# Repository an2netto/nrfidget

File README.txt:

A POV fidget spinner based on nRF52832

pcb - KiCAD design
sim - a simulator with 74HC595 shift register, SS413A Hall sensor and Nokia 5110 LCD

still in progress

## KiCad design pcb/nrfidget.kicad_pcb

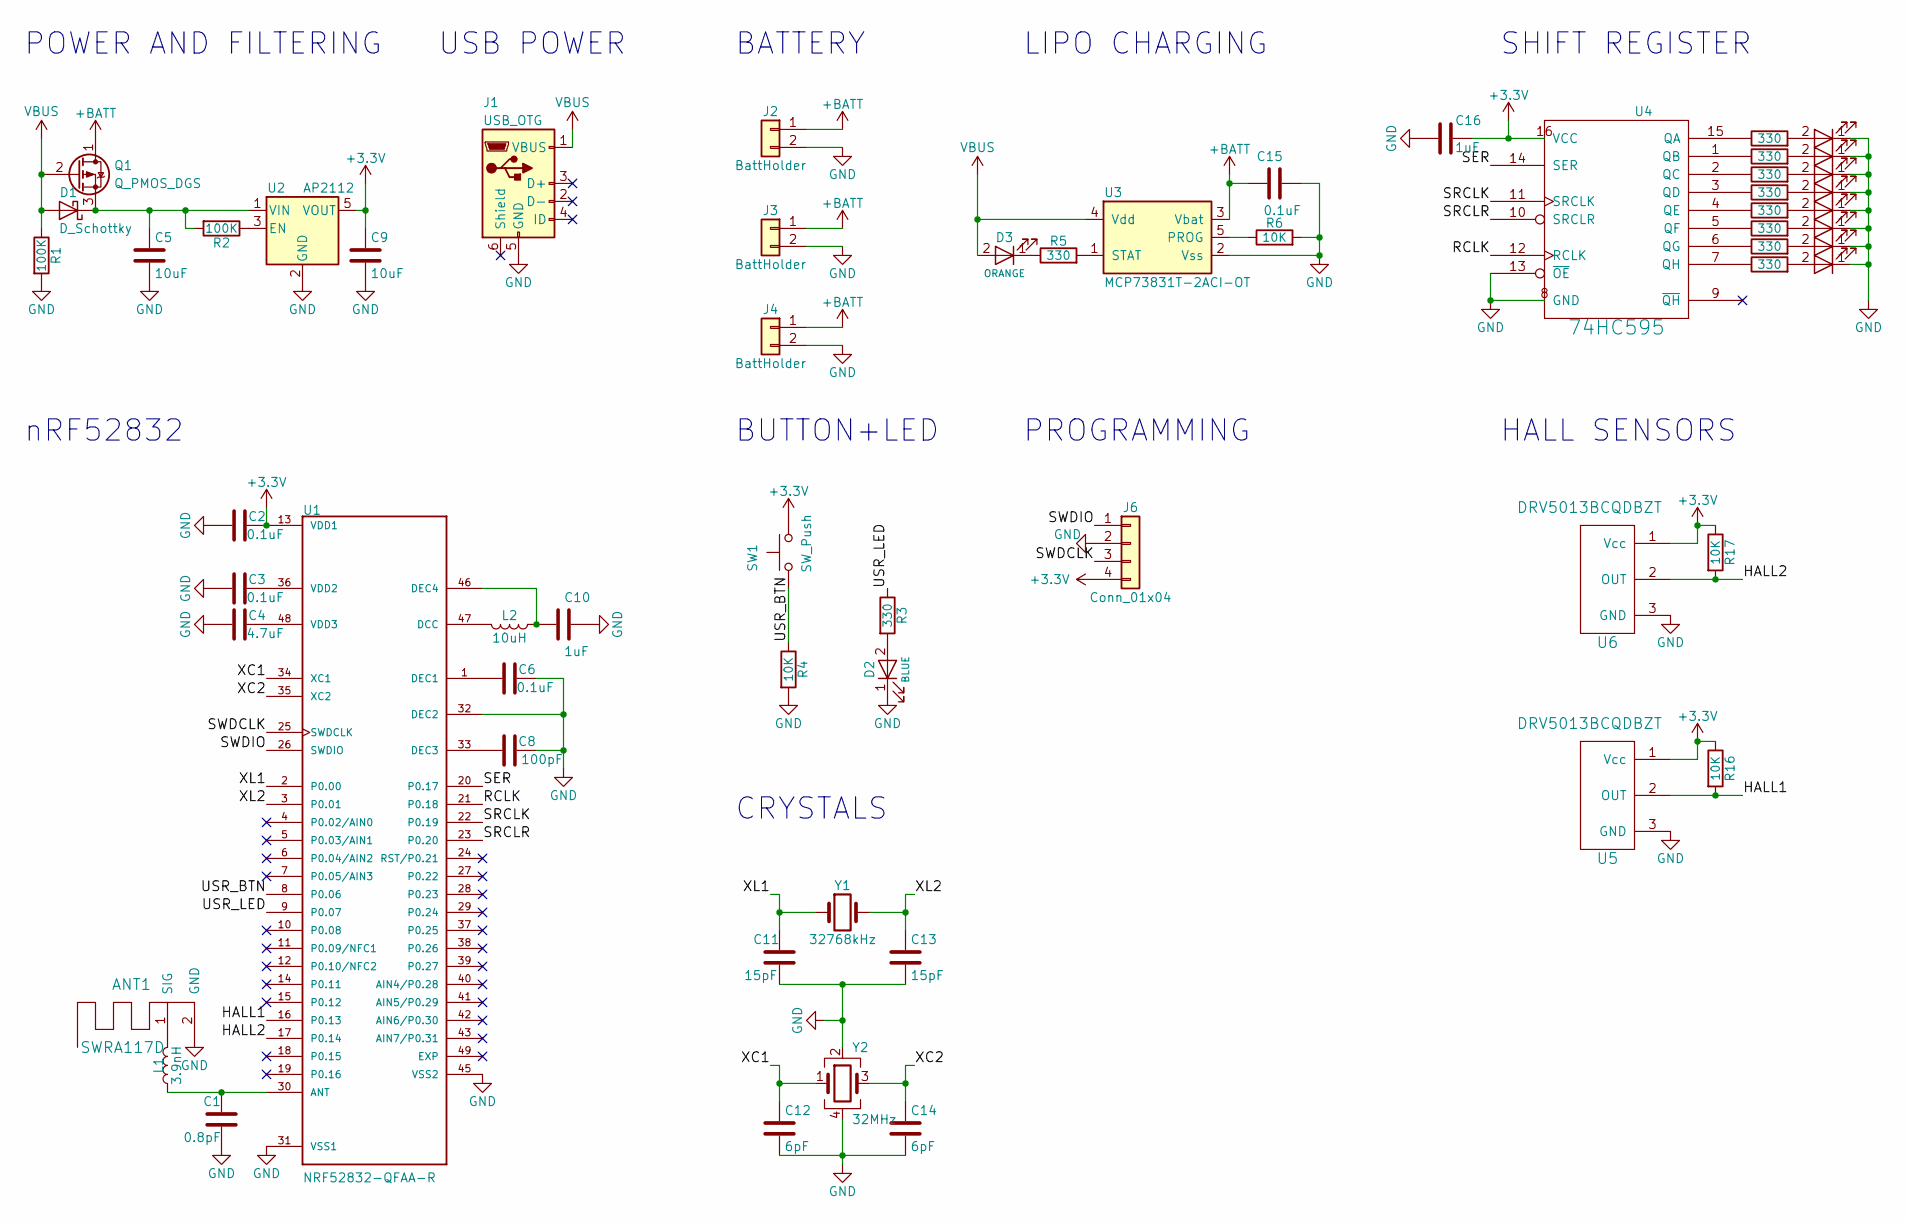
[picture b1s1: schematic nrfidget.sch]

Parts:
ANT1: SWRA117D; Texas_SWRA117D_2.4GHz_Left
C1: 0.8pF; C_0402
C2, C3, C6, C15: 0.1uF; C_0402
C4: 4.7uF; C_0603_HandSoldering
C5, C9: 10uF; C_0603_HandSoldering
C8: 100pF; C_0402
C10: 1uF; C_0603_HandSoldering
C11, C13: 15pF; C_0402
C12, C14: 6pF; C_0402
C16: 1uF; C_0402
D1: D_Schottky; D_SOD-123
D2: BLUE; LED_0603_HandSoldering
D3: ORANGE; LED_0603_HandSoldering
D4, D5, D6, D7, D8, D9, D10, D11: LED; LED_0603_HandSoldering
J1: USB_OTG; USB_Micro-B_Molex-105017-0001
J2, J3, J4: BattHolder; 3003
J6: Conn_01x04; Pin_Header_Straight_1x04_Pitch1.27mm
L1: 3.9nH; L_0402
L2: 10uH; L_0603_HandSoldering
Q1: Q_PMOS_DGS; SOT-23_Handsoldering
R1, R2: 100K; R_0402
R3, R5, R7, R8, R9, R10, R11, R12, R13, R14: 330; R_0402
R4, R6, R16, R17: 10K; R_0402
SW1: SW_Push; SW_SPST_PTS645
U1: NRF52832-QFAA-R; QFN-48-1EP_6x6mm_P0.4mm_EP4.66x4.66mm
U2: AP2112; SOT-23-5
U3: MCP73831T-2ACI-OT; SOT-23-5
U4: 74HC595; TSSOP-16_4.4x5mm_P0.65mm
U5, U6: DRV5013BCQDBZT; SOT-23
Y1: 32768kHz; Crystal_SMD_3215-2pin_3.2x1.5mm
Y2: 32MHz; Crystal_SMD_2016-4pin_2.0x1.6mm

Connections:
+3V3: C2.2, C9.1, C16.1, J6.4, R16.1, R17.1, SW1.1, U1.13 (VDD1), U2.5 (VOUT), U4.16 (VCC), U5.1 (Vcc), U6.1 (Vcc)
+BATT: C15.1, J2.1, J3.1, J4.1, Q1.1 (D), U3.3 (Vbat)
/HALL1: R16.2, U1.16 (P0.13), U5.2 (OUT)
/HALL2: R17.2, U1.17 (P0.14), U6.2 (OUT)
/RCLK: U1.21 (P0.18), U4.12 (RCLK)
/SER: U1.20 (P0.17), U4.14 (SER)
/SRCLK: U1.22 (P0.19), U4.11 (SRCLK)
/SRCLR: U1.23 (P0.20), U4.10 (SRCLR)
/SWDCLK: J6.3, U1.25 (SWDCLK)
/SWDIO: J6.1, U1.26 (SWDIO)
/USR_BTN: R4.1, SW1.2, U1.8 (P0.06)
/USR_LED: R3.1, U1.9 (P0.07)
/XC1: C12.1, U1.34 (XC1), Y2.1
/XC2: C14.1, U1.35 (XC2), Y2.3
/XL1: C11.1, U1.2 (P0.00), Y1.1
/XL2: C13.1, U1.3 (P0.01), Y1.2
GND: ANT1.2 (GND), C1.2, C2.1, C3.1, C4.1, C5.2, C6.2, C8.2, C9.2, C10.1, C11.2, C12.2, C13.2, C14.2, C15.2, C16.2, D2.1 (K), D4.1 (K), D5.1 (K), D6.1 (K), D7.1 (K), D8.1 (K), D9.1 (K), D10.1 (K), D11.1 (K), J1.5 (GND), J2.2, J3.2, J4.2, J6.2, R1.2, R4.2, R6.2, U1.31 (VSS1), U1.32 (DEC2), U1.45 (VSS2), U1.49 (EXP), U2.2 (GND), U3.2 (Vss), U4.8 (GND), U4.13 (~OE), U5.3 (GND), U6.3 (GND), Y2.2, Y2.4
unnamed: ANT1.1 (SIG), L1.1
unnamed: C1.1, L1.2, U1.30 (ANT)
unnamed: C3.2, U1.36 (VDD2)
unnamed: C4.2, U1.48 (VDD3)
unnamed: C5.1, D1.1 (K), Q1.3 (S), R2.2, U2.1 (VIN)
unnamed: C6.1, U1.1 (DEC1)
unnamed: C8.1, U1.33 (DEC3)
unnamed: C10.2, L2.1, U1.46 (DEC4)
unnamed: D2.2 (A), R3.2
unnamed: D3.1 (K), R5.1
unnamed: D4.2 (A), R7.2
unnamed: D5.2 (A), R8.2
unnamed: D6.2 (A), R9.2
unnamed: D7.2 (A), R10.2
unnamed: D8.2 (A), R11.2
unnamed: D9.2 (A), R12.2
unnamed: D10.2 (A), R13.2
unnamed: D11.2 (A), R14.2
unnamed: L2.2, U1.47 (DCC)
unnamed: R2.1, U2.3 (EN)
unnamed: R5.2, U3.1 (STAT)
unnamed: R6.1, U3.5 (PROG)
unnamed: R7.1, U4.15 (QA)
unnamed: R8.1, U4.1 (QB)
unnamed: R9.1, U4.2 (QC)
unnamed: R10.1, U4.3 (QD)
unnamed: R11.1, U4.4 (QE)
unnamed: R12.1, U4.5 (QF)
unnamed: R13.1, U4.6 (QG)
unnamed: R14.1, U4.7 (QH)
VBUS: D1.2 (A), D3.2 (A), J1.1 (VBUS), Q1.2 (G), R1.1, U3.4 (Vdd)

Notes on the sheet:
SHIFT REGISTER
BUTTON+LED
BATTERY
USB POWER
POWER AND FILTERING
nRF52832
CRYSTALS
LIPO CHARGING
PROGRAMMING
HALL SENSORS

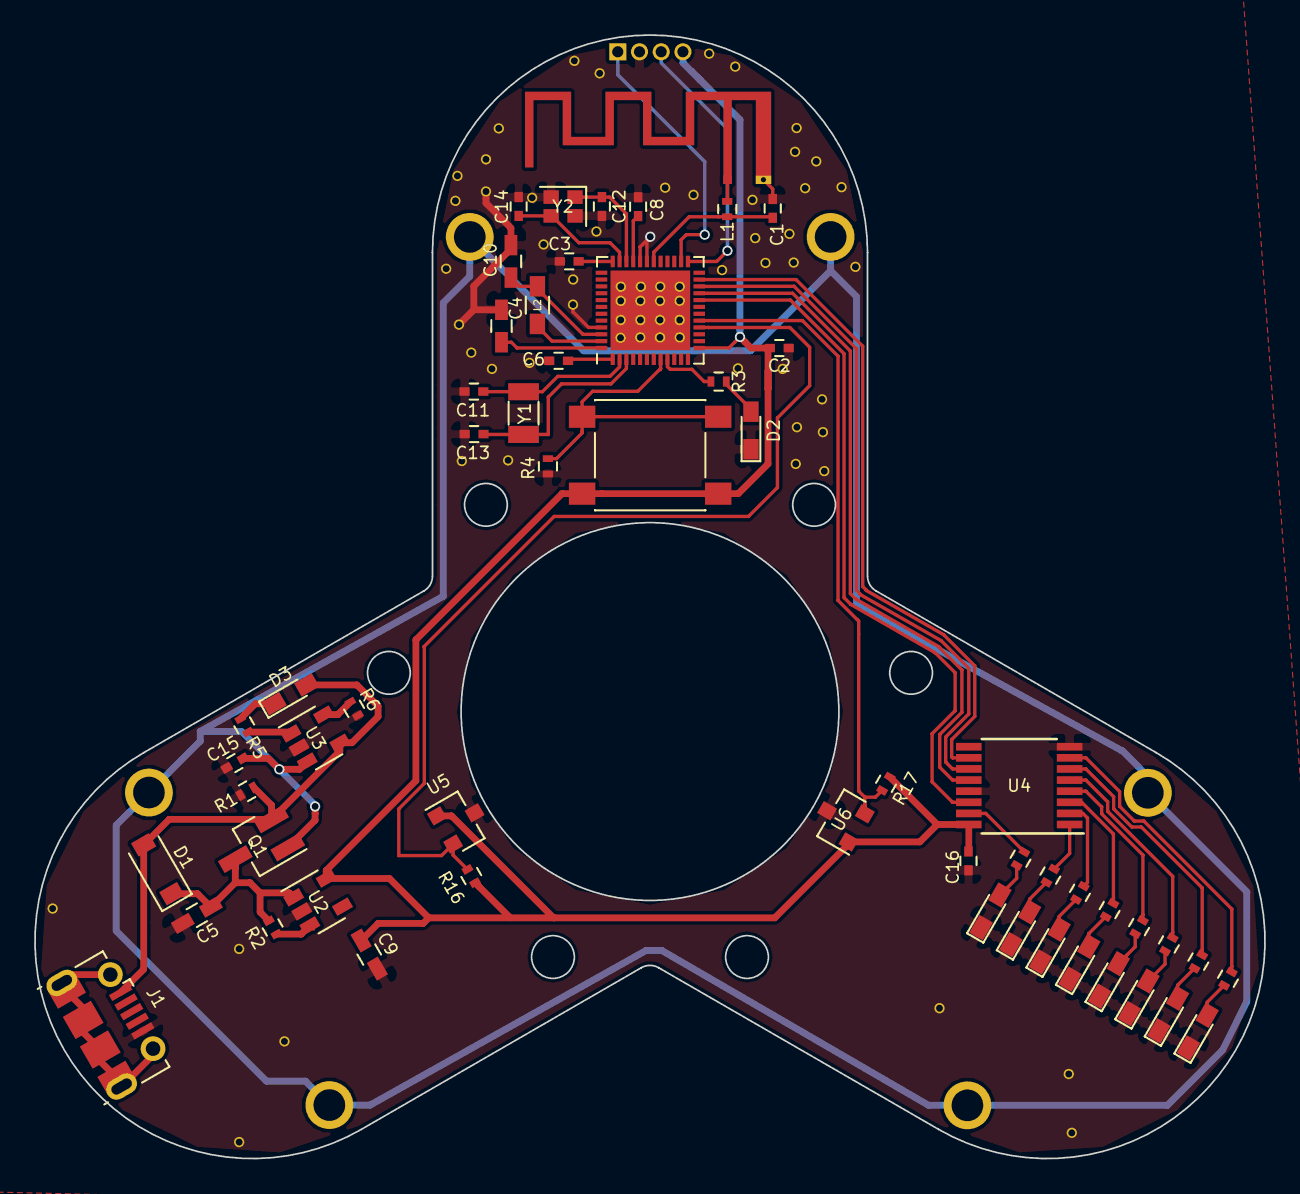
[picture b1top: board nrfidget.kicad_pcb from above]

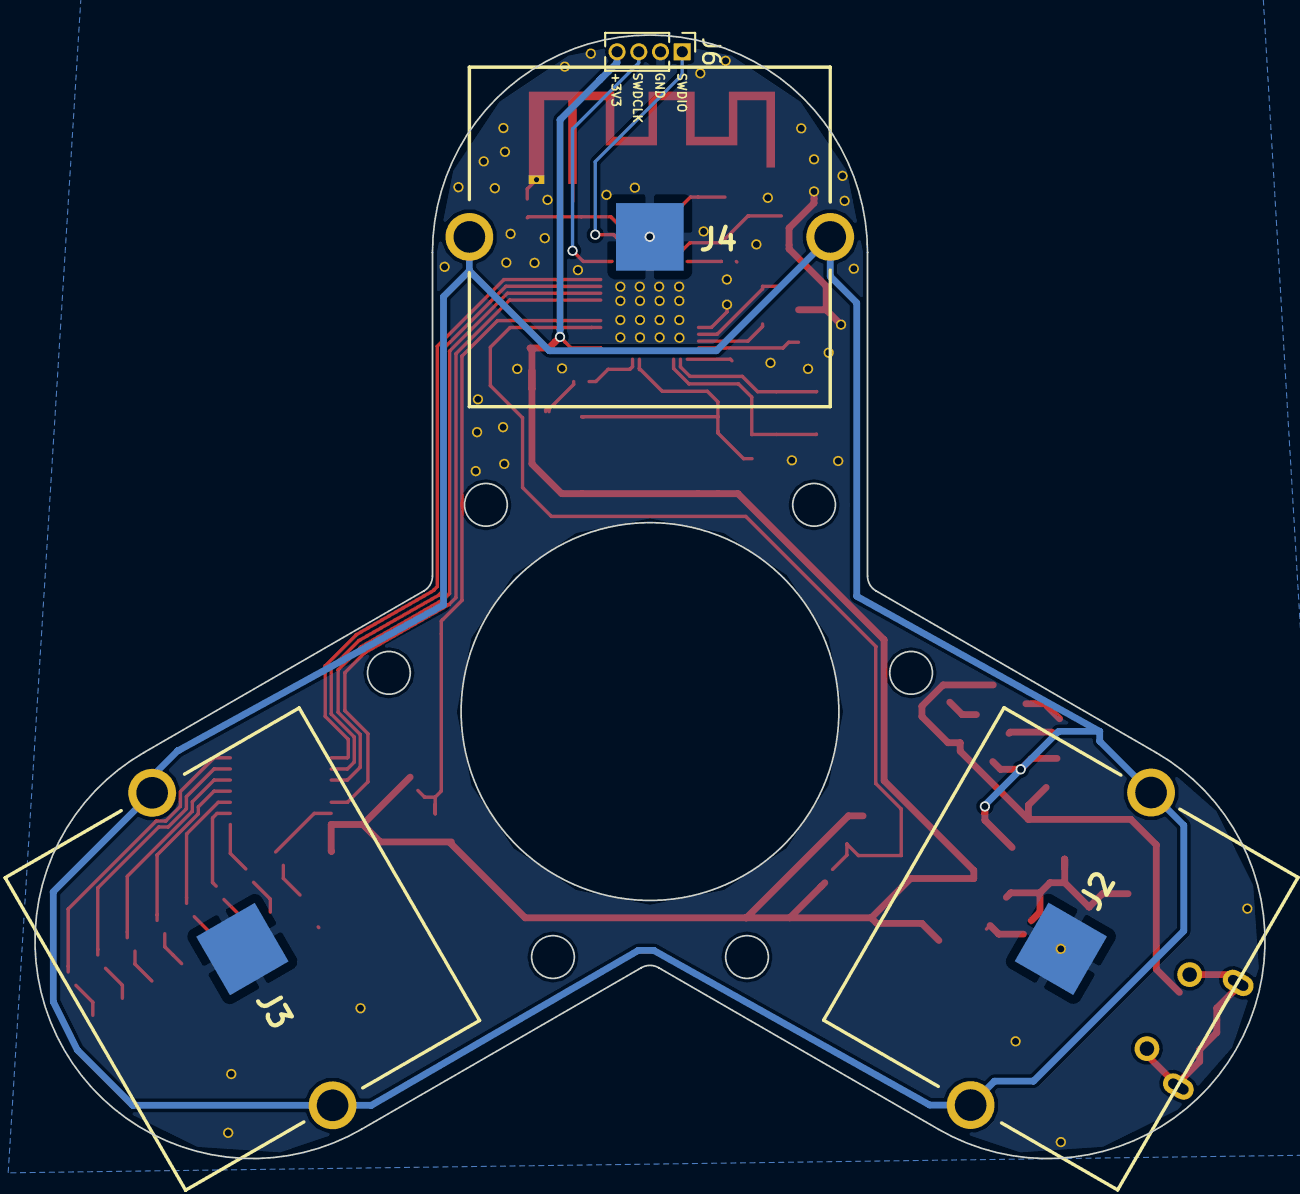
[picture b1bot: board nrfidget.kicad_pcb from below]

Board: 2 copper layers, 71.9 x 65.7 mm, 60 parts (4 on the bottom side), 48 nets.

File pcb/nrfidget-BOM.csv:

Refs,value,manpt#,shop,datasheet,footprint,
ANT1,SWRA117D,,,,RF_Antenna:Texas_SWRA117D_2.4GHz_Left,
C1,0.8pF,GJM1555C1HR80WB01D,,,Capacitors_SMD:C_0402,
C10,1uF,GCM188R71C105KA64D,https://www.rcscomponents.kiev.ua/product/1uf-16v-x7r-10-060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,,Capacitors_SMD:C_0603_HandSoldering,
C11,12pF,C0402N120J500NU-Hitano,https://www.rcscomponents.kiev.ua/product/12pf-50v-5-np0-040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,,Capacitors_SMD:C_0402,
C12,12pF,C0402N120J500NU-Hitano,https://www.rcscomponents.kiev.ua/product/12pf-50v-5-np0-040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,,Capacitors_SMD:C_0402,
C13,12pF,C0402N120J500NU-Hitano,https://www.rcscomponents.kiev.ua/product/12pf-50v-5-np0-040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,,Capacitors_SMD:C_0402,
C14,12pF,C0402N120J500NU-Hitano,https://www.rcscomponents.kiev.ua/product/12pf-50v-5-np0-040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,,Capacitors_SMD:C_0402,
C15,0.1uF,100nF 50V 10% X7R,https://www.rcscomponents.kiev.ua/product/100nf-50v-10-x7r-0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 ,,Capacitors_SMD:C_0402,
C16,1uF,"1uF 6,3V 10% X5R",https://www.rcscomponents.kiev.ua/product/1uf-6-3v-10-x5r-04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,,Capacitors_SMD:C_0402,
C2,0.1uF,100nF 50V 10% X7R,https://www.rcscomponents.kiev.ua/product/100nf-50v-10-x7r-0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 ,,Capacitors_SMD:C_0402,
C3,0.1uF,100nF 50V 10% X7R,https://www.rcscomponents.kiev.ua/product/100nf-50v-10-x7r-0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 ,,Capacitors_SMD:C_0402,
C4,4.7uF,"4,7uF 6,3V X5R 10%",https://www.rcscomponents.kiev.ua/product/4-7uf-6-3v-x5r-10-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,,Capacitors_SMD:C_0603_HandSoldering,
C5,10uF,"10uF 6,3V X5R 10%",https://www.rcscomponents.kiev.ua/product/10uf-6-3v-x5r-10-0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,,Capacitors_SMD:C_0603_HandSoldering,
C6,0.1uF,100nF 50V 10% X7R,https://www.rcscomponents.kiev.ua/product/100nf-50v-10-x7r-0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 ,,Capacitors_SMD:C_0402,
C8,100pF,100pF 50V 5% NP0,https://www.rcscomponents.kiev.ua/product/100pf-50v-5-np0-04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,,Capacitors_SMD:C_0402,
C9,10uF,"10uF 6,3V X5R 10%",https://www.rcscomponents.kiev.ua/product/10uf-6-3v-x5r-10-0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,,Capacitors_SMD:C_0603_HandSoldering,
D1,D_Schottky,MBR120LSFT1G,https://imrad.com.ua/ru/mbr120lsft1g,,Diodes_SMD:D_SOD-123,
D10,LED,LTST-C190TBKT,https://www.rcscomponents.kiev.ua/product/ltst-c190tbkt_121694.html,,LEDs:LED_0603_HandSoldering,
D11,LED,LTST-C190TBKT,https://www.rcscomponents.kiev.ua/product/ltst-c190tbkt_121694.html,,LEDs:LED_0603_HandSoldering,
D2,BLUE,LTST-C190TBKT,https://www.rcscomponents.kiev.ua/product/ltst-c190tbkt_121694.html,,LEDs:LED_0603_HandSoldering,
D3,ORANGE,KPT-1608SEW-E-Kingbright,https://www.rcscomponents.kiev.ua/product/svetodiod-0603-ora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,,LEDs:LED_0603_HandSoldering,
D4,LED,LTST-C190TBKT,https://www.rcscomponents.kiev.ua/product/ltst-c190tbkt_121694.html,,LEDs:LED_0603_HandSoldering,
D5,LED,LTST-C190TBKT,https://www.rcscomponents.kiev.ua/product/ltst-c190tbkt_121694.html,,LEDs:LED_0603_HandSoldering,
D6,LED,LTST-C190TBKT,https://www.rcscomponents.kiev.ua/product/ltst-c190tbkt_121694.html,,LEDs:LED_0603_HandSoldering,
D7,LED,LTST-C190TBKT,https://www.rcscomponents.kiev.ua/product/ltst-c190tbkt_121694.html,,LEDs:LED_0603_HandSoldering,
D8,LED,LTST-C190TBKT,https://www.rcscomponents.kiev.ua/product/ltst-c190tbkt_121694.html,,LEDs:LED_0603_HandSoldering,
D9,LED,LTST-C190TBKT,https://www.rcscomponents.kiev.ua/product/ltst-c190tbkt_121694.html,,LEDs:LED_0603_HandSoldering,
J1,USB_OTG,MX-105017-0001,https://www.rcscomponents.kiev.ua/product/micro-usb-tip-b-gn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,,Connectors_USB:USB_Micro-B_Vertical_Molex-105133-0001,
J2,BattHolder,BATKEYS3003,https://www.rcscomponents.kiev.ua/product/derzhatel-na-platu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,,Battery:BatteryHolder_Keystone_3034_1x20mm,
J3,BattHolder,BATKEYS3003,https://www.rcscomponents.kiev.ua/product/derzhatel-na-platu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,,Battery:BatteryHolder_Keystone_3034_1x20mm,
J4,BattHolder,BATKEYS3003,https://www.rcscomponents.kiev.ua/product/derzhatel-na-platu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,,Battery:BatteryHolder_Keystone_3034_1x20mm,
J6,Conn_01x04,"PLL1,27-12",https://www.rcscomponents.kiev.ua/product/pll1-27-12-ch02122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,,Pin_Headers:Pin_Header_Straight_1x04_Pitch1.27mm,
L1,3.9nH,SDWL1608C3N9SSTF,,,Inductors_SMD:L_0402,
L2,10uH,10uH 10% 0603,https://www.rcscomponents.kiev.ua/product/10uh-10-0603-smi06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,,Inductors_SMD:L_0603_HandSoldering,
Q1,Q_PMOS_DGS,DMP2045U == IRLML6401TRPBF,https://imrad.com.ua/ru/irlml6401trpbf,https://www.diodes.com/assets/Datasheets/DMP2045U.pdf,TO_SOT_Packages_SMD:SOT-23_Handsoldering,
R1,100K,RC0402FR-100KR-Hitano,https://www.rcscomponents.kiev.ua/product/100-kohm-1-1-16w-5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,,Resistors_SMD:R_0402,
R10,330,RC0402JR-330R-Hitano,https://www.rcscomponents.kiev.ua/product/330-ohm-5-1-16w-50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 ,,Resistors_SMD:R_0402,
R11,330,RC0402JR-330R-Hitano,https://www.rcscomponents.kiev.ua/product/330-ohm-5-1-16w-50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 ,,Resistors_SMD:R_0402,
R12,330,RC0402JR-330R-Hitano,https://www.rcscomponents.kiev.ua/product/330-ohm-5-1-16w-50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 ,,Resistors_SMD:R_0402,
R13,330,RC0402JR-330R-Hitano,https://www.rcscomponents.kiev.ua/product/330-ohm-5-1-16w-50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 ,,Resistors_SMD:R_0402,
R14,330,RC0402JR-330R-Hitano,https://www.rcscomponents.kiev.ua/product/330-ohm-5-1-16w-50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 ,,Resistors_SMD:R_0402,
R16,10K,RC0402FR-10KR-Hitano,https://www.rcscomponents.kiev.ua/product/10-kohm-1-1-16w-50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,,Resistors_SMD:R_0402,
R17,10K,RC0402FR-10KR-Hitano,https://www.rcscomponents.kiev.ua/product/10-kohm-1-1-16w-50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,,Resistors_SMD:R_0402,
R2,100K,RC0402FR-100KR-Hitano,https://www.rcscomponents.kiev.ua/product/100-kohm-1-1-16w-5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,,Resistors_SMD:R_0402,
R3,330,RC0402JR-330R-Hitano,https://www.rcscomponents.kiev.ua/product/330-ohm-5-1-16w-50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 ,,Resistors_SMD:R_0402,
R4,10K,RC0402FR-10KR-Hitano,https://www.rcscomponents.kiev.ua/product/10-kohm-1-1-16w-50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,,Resistors_SMD:R_0402,
R5,330,RC0402JR-330R-Hitano,https://www.rcscomponents.kiev.ua/product/330-ohm-5-1-16w-50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 ,,Resistors_SMD:R_0402,
R6,10K,RC0402FR-10KR-Hitano,https://www.rcscomponents.kiev.ua/product/10-kohm-1-1-16w-50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,,Resistors_SMD:R_0402,
R7,330,RC0402JR-330R-Hitano,https://www.rcscomponents.kiev.ua/product/330-ohm-5-1-16w-50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 ,,Resistors_SMD:R_0402,
R8,330,RC0402JR-330R-Hitano,https://www.rcscomponents.kiev.ua/product/330-ohm-5-1-16w-50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 ,,Resistors_SMD:R_0402,
R9,330,RC0402JR-330R-Hitano,https://www.rcscomponents.kiev.ua/product/330-ohm-5-1-16w-50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 ,,Resistors_SMD:R_0402,
SW1,SW_Push,KLS7-TS6611-1.5-180,https://www.rcscomponents.kiev.ua/product/knopka-adtsm61rvtr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 ,,Buttons_Switches_SMD:SW_SPST_PTS645,
U1,NRF52832-QFAA-R,NRF52832-QFAA-R7,https://prom.ua/p537853714-bluetooth-priyomo-peredatchik,,https://eu.mouser.com/datasheet/2/297/nRF52832_PS_v1.3-1117956.pdf,Package_DFN_QFN:QFN-48-1EP_6x6mm_P0.4mm_EP4.66x4.66mm
U2,AP2112,AP2112K-3.3TRG1,https://prom.ua/p701898586-mikroshema-ap2112k-33trg1,,https://www.diodes.com/assets/Datasheets/AP2112.pdf,TO_SOT_Packages_SMD:SOT-23-5
U3,MCP73831T-2ACI-OT,MCP73831T-2ATI/OT,https://imrad.com.ua/ru/mcp73831t-2ati-ot,https://cdn.sparkfun.com/assets/learn_tutorials/6/9/5/MCP738312.pdf,TO_SOT_Packages_SMD:SOT-23-5,
U4,74HC595,"74HC595BQ,115",http://www.kosmodrom.com.ua/el.php?name=MC74HC595ADTR2G,https://www.onsemi.com/pub/Collateral/MC74HC595A-D.PDF,Package_SO:TSSOP-16_4.4x5mm_P0.65mm,
U5,DRV5013BCQDBZT,DRV5013FAQDBZR,http://www.kosmodrom.com.ua/el.php?name=DRV5013BCQDBZT,http://www.ti.com/lit/ds/symlink/drv5013.pdf,TO_SOT_Packages_SMD:SOT-23,
U6,DRV5013BCQDBZT,DRV5013FAQDBZR,http://www.kosmodrom.com.ua/el.php?name=DRV5013BCQDBZT,http://www.ti.com/lit/ds/symlink/drv5013.pdf,TO_SOT_Packages_SMD:SOT-23,
Y1,32768kHz,SC-32S32.768kHz20PPM9pF,https://eu.mouser.com/ProductDetail/CTS-Electronic-Component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 ,https://eu.mouser.com/datasheet/2/96/008-0354-0_A_TF32_Serie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,Crystals:Crystal_SMD_3215-2pin_3.2x1.5mm,
Y2,32MHz,X201632MKD4SI,https://eu.mouser.com/ProductDetail/IQD/LFXTAL061700Cutt?qs=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,https://eu.mouser.com/datasheet/2/741/LFXTAL061700Bulk-1000830.pdf,Crystals:Crystal_SMD_2016-4pin_2.0x1.6mm,

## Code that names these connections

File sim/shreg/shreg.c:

/** @file
  * @brief 74HC595 driver
  *
  * SRCLK  pin 11 connected to SHREG_SRCLK_PIN
  * RCLK   pin 12 connected to SHREG_RCLK_PIN
  * SER    pin 14 connected to SHREG_SER_PIN
  * VCC    pin 16 3.3V
  * GND    pin 8  GND
  */

#include "shreg.h"
#include "nrfx_spim.h"
#include "nrfx_gpiote.h"
#include "app_error.h"

static const nrfx_spim_t spi = NRFX_SPIM_INSTANCE(1);
static uint8_t ser_buf; /**< 8-bit serial buffer */

static void gpio_init(void)
{
    ret_code_t err_code;

    if (nrfx_gpiote_is_init() == false) {
      err_code = nrfx_gpiote_init();
      APP_ERROR_CHECK(err_code);
    }

    nrfx_gpiote_out_config_t out_config = NRFX_GPIOTE_CONFIG_OUT_SIMPLE(false);

    err_code = nrfx_gpiote_out_init(SHREG_RCLK_PIN, &out_config);
    APP_ERROR_CHECK(err_code);
}

static void spi_init(void)
{
    nrfx_spim_config_t spi_config = NRFX_SPIM_DEFAULT_CONFIG;
    spi_config.mosi_pin = SHREG_SER_PIN;
    spi_config.sck_pin  = SHREG_SRCLK_PIN;
    spi_config.bit_order = NRF_SPIM_BIT_ORDER_LSB_FIRST;
    // spi_config.ss_pin  = SHREG_RCLK_PIN;
    // spi_config.ss_active_high = false;
    spi_config.frequency = NRF_SPIM_FREQ_1M;

    APP_ERROR_CHECK(nrfx_spim_init(&spi, &spi_config, NULL, NULL));
}

void shreg_init(void)
{
    gpio_init();
    spi_init();
}

void shreg_shift(uint8_t c)
{
    nrf_gpio_pin_clear(SHREG_RCLK_PIN);

    ser_buf = c;
    static const nrfx_spim_xfer_desc_t ser_xfer_desc = NRFX_SPIM_XFER_TX(&ser_buf, 1);
    APP_ERROR_CHECK(nrfx_spim_xfer(&spi, &ser_xfer_desc, NRFX_SPIM_FLAG_NO_XFER_EVT_HANDLER));

    nrf_gpio_pin_set(SHREG_RCLK_PIN);
}

void shreg_clear(void)
{
    shreg_shift(0x00);
}

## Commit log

2018-05-28 First commit: add sim and pcb
2018-05-29 plot schematic to pdf file
2018-05-29 minor fixes
